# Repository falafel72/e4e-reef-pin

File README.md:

# E4E Reef Pin
Central repository for the Reef Pin project at E4E UCSD.

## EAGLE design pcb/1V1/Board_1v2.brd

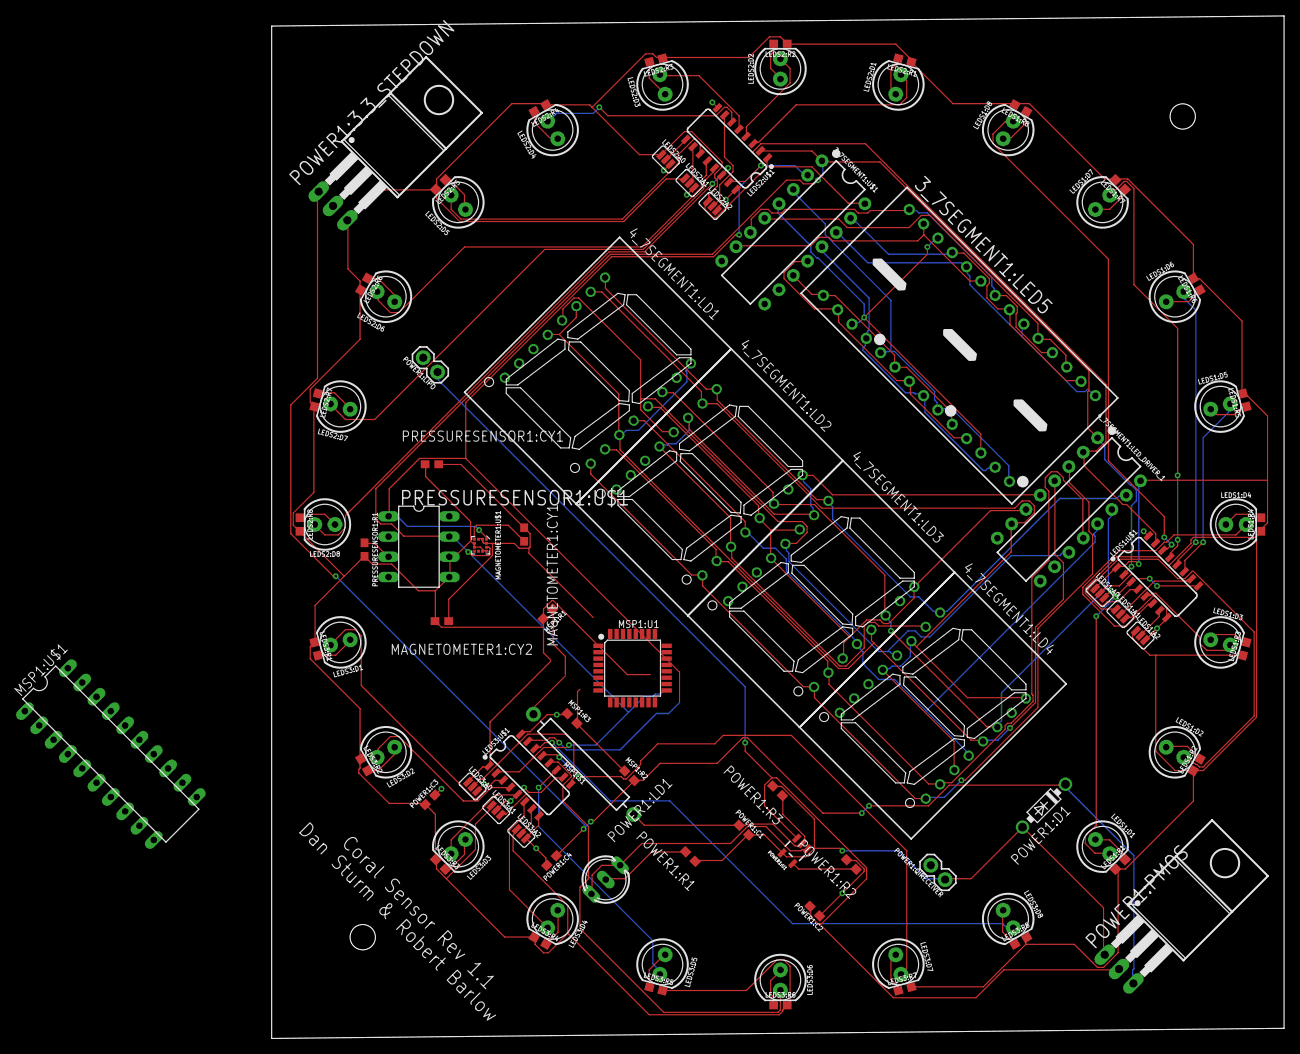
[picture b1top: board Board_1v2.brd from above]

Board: 2 copper layers, 127.0 x 128.3 mm, 93 parts (0 on the bottom side), 91 nets.

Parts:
3_7SEGMENT1:LED5: BA56-11EWA; BA/BC56
3_7SEGMENT1:U$1: MAX6958BAPE+; DIP16
4_7SEGMENT1:LD1, 4_7SEGMENT1:LD2, 4_7SEGMENT1:LD3, 4_7SEGMENT1:LD4: SA08-11; SA08
4_7SEGMENT1:LED_DRIVER_1: DIP16
LEDS1:A0, LEDS1:A1, LEDS1:A2, LEDS2:A0, LEDS2:A1, LEDS2:A2, LEDS3:A0, LEDS3:A1, LEDS3:A2: SMT-JUMPER_3_NO_SILK
LEDS1:D1, LEDS1:D2, LEDS1:D3, LEDS1:D4, LEDS1:D5, LEDS1:D6, LEDS1:D7, LEDS1:D8, LEDS2:D1, LEDS2:D2, LEDS2:D3, LEDS2:D4, LEDS2:D5, LEDS2:D6, LEDS2:D7, LEDS2:D8, LEDS3:D1, LEDS3:D2, LEDS3:D3, LEDS3:D4, LEDS3:D5, LEDS3:D6, LEDS3:D7, LEDS3:D8: LED_5MM
LEDS1:R1, LEDS1:R2, LEDS1:R3, LEDS1:R4, LEDS1:R5, LEDS1:R6, LEDS1:R7, LEDS1:R8, LEDS2:R1, LEDS2:R2, LEDS2:R3, LEDS2:R4, LEDS2:R5, LEDS2:R6, LEDS2:R7, LEDS2:R8, LEDS3:R1, LEDS3:R2, LEDS3:R3, LEDS3:R4, LEDS3:R5, LEDS3:R6, LEDS3:R7, LEDS3:R8: 100; 0603
LEDS1:U$1, LEDS2:U$1, LEDS3:U$1: TPIC2810D; SO16
MAGNETOMETER1:CY1, MAGNETOMETER1:CY2: 0.1uF; 0603
MAGNETOMETER1:U$1: LGA-12
MSP1:R1: 100; 0603
MSP1:R2, MSP1:R3: 100k; 0603
MSP1:S1: REED_SWITCH-PTH-GLASS; REED_SWITCH_GLASS
MSP1:U1: MCU-ATMEGA328P-AU(TQFP32); TQFP32-0.8-7X7MM
MSP1:U$1: MSP430G2452IN20; DIL20
POWER1:3.3_STEPDOWN: MCP1826S; T03B
POWER1:C1, POWER1:C2: 4.7uF; 0603
POWER1:C3, POWER1:C4: 10uF; 0603
POWER1:D1: 1N5817-B; DO41-7.6
POWER1:LD1: DUOLED-A-5MM
POWER1:LIPO, POWER1:QIRECEIVER: 1X02
POWER1:PMOS: IPP80P03P4L-04; T03B
POWER1:R1: 470; 0603
POWER1:R2: 2.0k; 0603
POWER1:R3: 100k; 0603
POWER1:U1: MCP73831; SOT23-5
PRESSURESENSOR1:CY1: 0.1uF; 0603
PRESSURESENSOR1:R1: 10k; 0603
PRESSURESENSOR1:U$1: MS5803-14BA; DIL8

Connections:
3.3V: 3_7SEGMENT1:U$1.16, 4_7SEGMENT1:LED_DRIVER_1.16, LEDS1:A0.1, LEDS1:A1.1, LEDS1:A2.1, LEDS1:R1.1, LEDS1:R2.1, LEDS1:R3.1, LEDS1:R4.1, LEDS1:R5.2, LEDS1:R6.2, LEDS1:R7.2, LEDS1:R8.2, LEDS1:U$1.1, LEDS2:A0.1, LEDS2:A1.1, LEDS2:A2.1, LEDS2:R1.1, LEDS2:R2.1, LEDS2:R3.1, LEDS2:R4.1, LEDS2:R5.2, LEDS2:R6.2, LEDS2:R7.2, LEDS2:R8.2, LEDS2:U$1.1, LEDS3:A0.1, LEDS3:A1.1, LEDS3:A2.1, LEDS3:R1.1, LEDS3:R2.1, LEDS3:R3.1, LEDS3:R4.1, LEDS3:R5.2, LEDS3:R6.2, LEDS3:R7.2, LEDS3:R8.2, LEDS3:U$1.1, MAGNETOMETER1:CY2.2, MAGNETOMETER1:U$1.5, MAGNETOMETER1:U$1.6, MAGNETOMETER1:U$1.9, MAGNETOMETER1:U$1.10, MSP1:R1.2, MSP1:U1.6, MSP1:U1.29, POWER1:3.3_STEPDOWN.3, POWER1:C3.1, PRESSURESENSOR1:CY1.1, PRESSURESENSOR1:R1.2, PRESSURESENSOR1:U$1.5, PRESSURESENSOR1:U$1.6
3_7SEGMENT1:N$1: 3_7SEGMENT1:LED5.3, 3_7SEGMENT1:LED5.12, 3_7SEGMENT1:LED5.26, 3_7SEGMENT1:U$1.4
3_7SEGMENT1:N$2: 3_7SEGMENT1:LED5.5, 3_7SEGMENT1:LED5.9, 3_7SEGMENT1:LED5.14, 3_7SEGMENT1:U$1.3
3_7SEGMENT1:N$8: 3_7SEGMENT1:LED5.16, 3_7SEGMENT1:LED5.21, 3_7SEGMENT1:LED5.25, 3_7SEGMENT1:U$1.15
3_7SEGMENT1:N$9: 3_7SEGMENT1:LED5.15, 3_7SEGMENT1:LED5.20, 3_7SEGMENT1:LED5.24, 3_7SEGMENT1:U$1.14
3_7SEGMENT1:N$10: 3_7SEGMENT1:LED5.4, 3_7SEGMENT1:LED5.8, 3_7SEGMENT1:LED5.13, 3_7SEGMENT1:U$1.13
3_7SEGMENT1:N$11: 3_7SEGMENT1:LED5.2, 3_7SEGMENT1:LED5.7, 3_7SEGMENT1:LED5.11, 3_7SEGMENT1:U$1.12
3_7SEGMENT1:N$26: 3_7SEGMENT1:LED5.1, 3_7SEGMENT1:LED5.6, 3_7SEGMENT1:LED5.10, 3_7SEGMENT1:U$1.11
3_7SEGMENT1:N$28: 3_7SEGMENT1:LED5.17, 3_7SEGMENT1:LED5.19, 3_7SEGMENT1:U$1.5
3_7SEGMENT1:N$29: 3_7SEGMENT1:LED5.23, 3_7SEGMENT1:LED5.27, 3_7SEGMENT1:U$1.7
3_7SEGMENT1:N$30: 3_7SEGMENT1:LED5.18, 3_7SEGMENT1:LED5.22, 3_7SEGMENT1:LED5.28, 3_7SEGMENT1:U$1.6
4_7SEGMENT1:N$1: 4_7SEGMENT1:LD1.1, 4_7SEGMENT1:LD2.1, 4_7SEGMENT1:LD3.1, 4_7SEGMENT1:LD4.1, 4_7SEGMENT1:LED_DRIVER_1.15
4_7SEGMENT1:N$2: 4_7SEGMENT1:LD1.14, 4_7SEGMENT1:LD2.14, 4_7SEGMENT1:LD3.14, 4_7SEGMENT1:LD4.14, 4_7SEGMENT1:LED_DRIVER_1.14
4_7SEGMENT1:N$3: 4_7SEGMENT1:LD1.12, 4_7SEGMENT1:LD2.12, 4_7SEGMENT1:LD3.12, 4_7SEGMENT1:LD4.12, 4_7SEGMENT1:LED_DRIVER_1.13
4_7SEGMENT1:N$4: 4_7SEGMENT1:LD1.10, 4_7SEGMENT1:LD2.10, 4_7SEGMENT1:LD3.10, 4_7SEGMENT1:LD4.10, 4_7SEGMENT1:LED_DRIVER_1.12
4_7SEGMENT1:N$5: 4_7SEGMENT1:LD1.4, 4_7SEGMENT1:LD2.4, 4_7SEGMENT1:LD3.4, 4_7SEGMENT1:LD4.4, 4_7SEGMENT1:LED_DRIVER_1.11
4_7SEGMENT1:N$6: 4_7SEGMENT1:LD1.3, 4_7SEGMENT1:LD1.5, 4_7SEGMENT1:LD1.11, 4_7SEGMENT1:LD1.16, 4_7SEGMENT1:LD3.13, 4_7SEGMENT1:LD4.13, 4_7SEGMENT1:LED_DRIVER_1.4
4_7SEGMENT1:N$7: 4_7SEGMENT1:LD1.9, 4_7SEGMENT1:LD2.9, 4_7SEGMENT1:LD3.9, 4_7SEGMENT1:LD4.9, 4_7SEGMENT1:LED_DRIVER_1.3
4_7SEGMENT1:N$9: 4_7SEGMENT1:LD1.2, 4_7SEGMENT1:LD2.2, 4_7SEGMENT1:LD4.3, 4_7SEGMENT1:LD4.5, 4_7SEGMENT1:LD4.11, 4_7SEGMENT1:LD4.16, 4_7SEGMENT1:LED_DRIVER_1.7
4_7SEGMENT1:N$12: 4_7SEGMENT1:LD2.3, 4_7SEGMENT1:LD2.5, 4_7SEGMENT1:LD2.11, 4_7SEGMENT1:LD2.16, 4_7SEGMENT1:LD3.2, 4_7SEGMENT1:LD4.2, 4_7SEGMENT1:LED_DRIVER_1.5
4_7SEGMENT1:N$13: 4_7SEGMENT1:LD1.13, 4_7SEGMENT1:LD2.13, 4_7SEGMENT1:LD3.3, 4_7SEGMENT1:LD3.5, 4_7SEGMENT1:LD3.11, 4_7SEGMENT1:LD3.16, 4_7SEGMENT1:LED_DRIVER_1.6
GND: 3_7SEGMENT1:U$1.8, 4_7SEGMENT1:LED_DRIVER_1.8, LEDS1:A0.3, LEDS1:A1.3, LEDS1:A2.3, LEDS1:U$1.8, LEDS1:U$1.16, LEDS2:A0.3, LEDS2:A1.3, LEDS2:A2.3, LEDS2:U$1.8, LEDS2:U$1.16, LEDS3:A0.3, LEDS3:A1.3, LEDS3:A2.3, LEDS3:U$1.8, LEDS3:U$1.16, MAGNETOMETER1:CY1.1, MAGNETOMETER1:CY2.1, MAGNETOMETER1:U$1.2, MAGNETOMETER1:U$1.3, MAGNETOMETER1:U$1.12, MSP1:R3.1, MSP1:S1.P$1, MSP1:U1.3, POWER1:3.3_STEPDOWN.2, POWER1:C1.1, POWER1:C2.1, POWER1:C3.2, POWER1:C4.2, POWER1:LIPO.2, POWER1:QIRECEIVER.2, POWER1:R2.2, POWER1:R3.1, POWER1:U1.2, PRESSURESENSOR1:CY1.2, PRESSURESENSOR1:U$1.2
LEDS1:N$1: LEDS1:D1.K, LEDS1:U$1.3
LEDS1:N$2: LEDS1:D2.K, LEDS1:U$1.4
LEDS1:N$3: LEDS1:D3.K, LEDS1:U$1.5
LEDS1:N$4: LEDS1:D4.K, LEDS1:U$1.6
LEDS1:N$5: LEDS1:D5.K, LEDS1:U$1.11
LEDS1:N$6: LEDS1:D6.K, LEDS1:U$1.12
LEDS1:N$7: LEDS1:D7.K, LEDS1:U$1.13
LEDS1:N$8: LEDS1:D8.K, LEDS1:U$1.14
LEDS1:N$9: LEDS1:A2.2, LEDS1:U$1.7
LEDS1:N$10: LEDS1:A1.2, LEDS1:U$1.10
LEDS1:N$11: LEDS1:A0.2, LEDS1:U$1.9
LEDS1:N$12: LEDS1:D5.A, LEDS1:R5.1
LEDS1:N$13: LEDS1:D6.A, LEDS1:R6.1
LEDS1:N$14: LEDS1:D7.A, LEDS1:R7.1
LEDS1:N$15: LEDS1:D8.A, LEDS1:R8.1
LEDS1:N$16: LEDS1:D1.A, LEDS1:R1.2
LEDS1:N$18: LEDS1:D2.A, LEDS1:R2.2
LEDS1:N$19: LEDS1:D3.A, LEDS1:R3.2
LEDS1:N$20: LEDS1:D4.A, LEDS1:R4.2
LEDS2:N$1: LEDS2:D1.K, LEDS2:U$1.3
LEDS2:N$2: LEDS2:D2.K, LEDS2:U$1.4
LEDS2:N$3: LEDS2:D3.K, LEDS2:U$1.5
LEDS2:N$4: LEDS2:D4.K, LEDS2:U$1.6
LEDS2:N$5: LEDS2:D5.K, LEDS2:U$1.11
LEDS2:N$6: LEDS2:D6.K, LEDS2:U$1.12
LEDS2:N$7: LEDS2:D7.K, LEDS2:U$1.13
LEDS2:N$8: LEDS2:D8.K, LEDS2:U$1.14
LEDS2:N$9: LEDS2:A2.2, LEDS2:U$1.7
LEDS2:N$10: LEDS2:A1.2, LEDS2:U$1.10
LEDS2:N$11: LEDS2:A0.2, LEDS2:U$1.9
LEDS2:N$12: LEDS2:D5.A, LEDS2:R5.1
LEDS2:N$13: LEDS2:D6.A, LEDS2:R6.1
LEDS2:N$14: LEDS2:D7.A, LEDS2:R7.1
LEDS2:N$15: LEDS2:D8.A, LEDS2:R8.1
LEDS2:N$16: LEDS2:D1.A, LEDS2:R1.2
LEDS2:N$18: LEDS2:D2.A, LEDS2:R2.2
LEDS2:N$19: LEDS2:D3.A, LEDS2:R3.2
LEDS2:N$20: LEDS2:D4.A, LEDS2:R4.2
LEDS3:N$1: LEDS3:D1.K, LEDS3:U$1.3
LEDS3:N$2: LEDS3:D2.K, LEDS3:U$1.4
LEDS3:N$3: LEDS3:D3.K, LEDS3:U$1.5
LEDS3:N$4: LEDS3:D4.K, LEDS3:U$1.6
LEDS3:N$5: LEDS3:D5.K, LEDS3:U$1.11
LEDS3:N$6: LEDS3:D6.K, LEDS3:U$1.12
LEDS3:N$7: LEDS3:D7.K, LEDS3:U$1.13
LEDS3:N$8: LEDS3:D8.K, LEDS3:U$1.14
LEDS3:N$9: LEDS3:A2.2, LEDS3:U$1.7
LEDS3:N$10: LEDS3:A1.2, LEDS3:U$1.10
LEDS3:N$11: LEDS3:A0.2, LEDS3:U$1.9
LEDS3:N$12: LEDS3:D5.A, LEDS3:R5.1
LEDS3:N$13: LEDS3:D6.A, LEDS3:R6.1
LEDS3:N$14: LEDS3:D7.A, LEDS3:R7.1
LEDS3:N$15: LEDS3:D8.A, LEDS3:R8.1
LEDS3:N$16: LEDS3:D1.A, LEDS3:R1.2
LEDS3:N$18: LEDS3:D2.A, LEDS3:R2.2
LEDS3:N$19: LEDS3:D3.A, LEDS3:R3.2
LEDS3:N$20: LEDS3:D4.A, LEDS3:R4.2
MAGNETOMETER1:N$3: MAGNETOMETER1:CY1.2, MAGNETOMETER1:U$1.4
MSP1:N$1: MSP1:R1.1, MSP1:S1.P$2, MSP1:U1.23
MSP1:N$2: MSP1:R2.1, MSP1:R3.2, MSP1:U1.24
unnamed: MSP1:R2.2, POWER1:3.3_STEPDOWN.1, POWER1:C4.1, POWER1:D1.C, POWER1:PMOS.3
unnamed: MSP1:U1.11, POWER1:LD1.CR, POWER1:LD1.CX, POWER1:U1.1
POWER1:N$2: POWER1:C2.2, POWER1:LIPO.1, POWER1:PMOS.2, POWER1:U1.3
POWER1:N$4: POWER1:C1.2, POWER1:D1.A, POWER1:PMOS.1, POWER1:QIRECEIVER.1, POWER1:R1.1, POWER1:R3.2, POWER1:U1.4
POWER1:N$6: POWER1:R2.1, POWER1:U1.5
POWER1:N$7: POWER1:LD1.A, POWER1:R1.2
PRESSURESENSOR1:N$1: PRESSURESENSOR1:R1.1, PRESSURESENSOR1:U$1.3
SCL: 3_7SEGMENT1:U$1.2, 4_7SEGMENT1:LED_DRIVER_1.2, LEDS1:U$1.15, LEDS2:U$1.15, LEDS3:U$1.15, MAGNETOMETER1:U$1.1, MSP1:U1.28, PRESSURESENSOR1:U$1.1
SDA: 3_7SEGMENT1:U$1.1, 4_7SEGMENT1:LED_DRIVER_1.1, LEDS1:U$1.2, LEDS2:U$1.2, LEDS3:U$1.2, MAGNETOMETER1:U$1.11, MSP1:U1.27, PRESSURESENSOR1:U$1.7

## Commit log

2019-05-01 added README
2019-05-03 Add files via upload
    numericLED test
2019-05-03 moved arduino sketch to correct folder
2019-05-03 Update test_numericLED.ino
    now you can change the LED using 4 digit numeric value
2019-05-03 Update test_numericLED.ino
    fixed minor errors
2019-05-04 added i2c communication to 7 segment display driver for depth reading
2019-05-06 Update e4e-reef-pin-logging.ino
    fixed the bugs, still minor issues
2019-05-17 Add files via upload
    test the bluetooth getting data from arduino
2019-05-17 Update get_data.py
    very buggy
2019-05-17 Add files via upload
    testing for bluetooth
2019-05-19 Update get_data.py
    now the test worked with the new if statement condition
2019-05-20 changed file location
2019-05-23 added external interrupts for charging and entering water
2019-05-24 PCB under folder 1.1, but file is named 1.2
2019-06-07 added low power functionality

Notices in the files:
parts and their libraries:
SparkFun-Switches: Licensing: Creative Commons ShareAlike 4.0 International - https://creativecommons.org/licenses/by-sa/4.0
